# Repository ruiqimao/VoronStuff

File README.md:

# VoronStuff
Collection of my Voron mods

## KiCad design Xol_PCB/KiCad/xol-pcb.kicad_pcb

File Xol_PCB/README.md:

# Xol PCB

This is a PCB made for Armchair Engineering's [Xol Toolhead](https://github.com/Armchair-Engineering/Xol-Toolhead), featuring:
* One hotend cooling fan JST-XH connectors
* Two part cooling  fan JST-XH connectors
* One heater Micro-Fit connector
* One thermistor Micro-Fit connector
* One Neopixel JST-XH connector
* Two auxiliary JST-XH connectors
* One extruder motor connector
* Selectable fan voltage (5V, Alt, 24V)
* Integrated mount for carriage screw

## BOM

In addition to the PCB, the following connectors are needed:

| Part | Quantity | Link |
|:-:|:-:|:-:|
| Molex Micro-Fit 3.0 430451600 | 1 | [DigiKey](https://www.digikey.com/en/products/detail/molex/0430451600/531424) |
| Molex Micro-Fit 3.0 430650200 | 2 | [DigiKey](https://www.digikey.com/en/products/detail/molex/0436500200/268989) |
| JST B2B-XH-A | 4 | [DigiKey](https://www.digikey.com/en/products/detail/jst-sales-america-inc./B2B-XH-A(LF)(SN)/1651045) |
| JST B3B-XH-A | 2 | [DigiKey](https://www.digikey.com/en/products/detail/jst-sales-america-inc./B3B-XH-A/1651046) |
| JST B4B-XH-A | 1 | [DigiKey](https://www.digikey.com/en/products/detail/jst-sales-america-inc./B4B-XH-A(LF)(SN)/1651047) |

## Pinout

From the point of view looking directly at the **wiring harness connector**:

| Pin | Usage | Pin | Usage |
|:-:|:-:|:-:|:-:|
| 1 | Neopixel | 9 | Hotend voltage |
| 2 | Part cooling fan ground | 10 | Hotend ground |
| 3 | Hotend fan ground | 11 | Alt voltage |
| 4 | Thermistor ground | 12 | Thermistor |
| 5 | Motor A1 | 13 | Motor B1 |
| 6 | Motor A2 | 14 | Motor B2 |
| 7 | Ground | 15 | Auxilary 1 |
| 8 | 5V | 16 | Auxiliary 2 |

## Selectable fan voltage

There are two sets of solder jumpers, one for each type of fan, that should be bridged to select the fan voltage.

## Extruder compatibility
The PCB and strain relief are designed with only the [Sherpa Mini](https://github.com/Annex-Engineering/Sherpa_Mini-Extruder) in mind. **Usage with other extruders may require the motor connector to be swapped to the back side.**

## Distribution board
Xol PCB is compatible with the [Xol distribution board](https://store.annex.engineering/collections/pcbs/products/carabiner-distribution-board-for-xol-toolhead) from Annex Engineering. See additional documentation [here](https://github.com/Annex-Engineering/Carabiner-Docs/tree/main/carabiner-distributor_xol).

### Alternatives
* A second Xol PCB can be used as a distribution board.
* The [Carabiner distribution board](https://github.com/Annex-Engineering/Carabiner-Docs/tree/main/carabiner-distributor) can be used as labeled with the following changes:

  | Distribution PCB | Xol PCB |
  |:-:|:-:|
  | ThChamb | RGB |
  | A1| GND |
  | A2 | AUX1 |
  | A3 | AUX2 |
  | A4 | 5V |

  Additional documentation [here](https://github.com/Annex-Engineering/Carabiner-Docs/tree/main/carabiner-distributor).

## Wiring harness

Xol PCB is compatible with the [Carabiner wiring harness](https://store.annex.engineering/products/carabiner-wiring-harness) from Annex Engineering. The long version is 1200mm, which may not sufficient for some printers.

| Printer | Compatible with Carabiner Harness |
|:-:|:-:|
| Trident 250mm | Yes |
| Trident 300mm | Yes |
| Trident 350mm | Likely (untested) |
| V2.4 250mm | Yes |
| V2.4 300mm | Yes with horizontal Z chain |
| V2.4 350mm | Unlikely (untested) |

### Alternatives

* **(Recommended)** Custom length Carabiner harness from [Annex Engineering](https://store.annex.engineering/collections/pcbs/products/carabiner-wiring-harness-custom-length-kit)
* **(Recommended)** 2.2 meter alternative from [Raven Mech](https://www.ravenmech.com/products/carabiner-pinned-cable-harness)
* Repin a 14+2 Stealthburner wiring harness (e.g. [14-pin](https://www.fabreeko.com/products/ldo-v2-4-or-trident-ptfe-toolhead-cable-1-9m-350mm-sized-build?variant=43114275537151) + [2-pin](https://kb-3d.com/store/printer-specific-harnesses/474-linneo-led-extension-harness-voron-stealth-burner-1642910819052.html) + [2x Molex Micro-Fit 3.0 0430251600](https://www.digikey.com/en/products/detail/molex/0430251600/531406?utm_adgroup=&utm_source=google&utm_medium=cpc&utm_campaign=PMax%20Supplier_Focus%20Supplier&utm_term=&utm_content=&gclid=EAIaIQobChMIsoGBzZrzgAMVJzmtBh1heQdKEAQYASABEgKG5PD_BwE))

## Beacon compatibility

The two AUX pins can be used for Beacon D- and D+ lines with some caveats:
* It is an untested use case
* There will be no more AUX pins left for endstop or filament sensors
* The traces are routed over ground plane splits
* 5V must be supplied from VBUS, meaning any fans running off of 5V will be powered by VBUS
* Only compatible with Annex harness, which has a twisted wire pair for D- and D+

## Purchasing

Xol PCB can currently be purchased from:

* :us: [X.R. Bunker](https://xrbunker.works/products/xol-toolhead-board-ruiqimao)
* :us: [Fabreeko](https://www.fabreeko.com/products/xol-toolhead-board-by-ruiqimao)
* :us: [West3D](https://west3d.com/products/xol-toolhead-pcb)
* :us: [Annex Engineering](https://store.annex.engineering/products/xol-toolhead-pcb)
* :canada: [NorthPrint3D](https://northprint3d.ca/product/xol-toolhead-toolboard-pcb)
* :uk: [JB3D](https://jb3d.uk/product/xol-toolhead-pcb-by-ruiqimao)
* :eu: [Lab4450](https://lab4450.com/product/xol-toolhead-board)

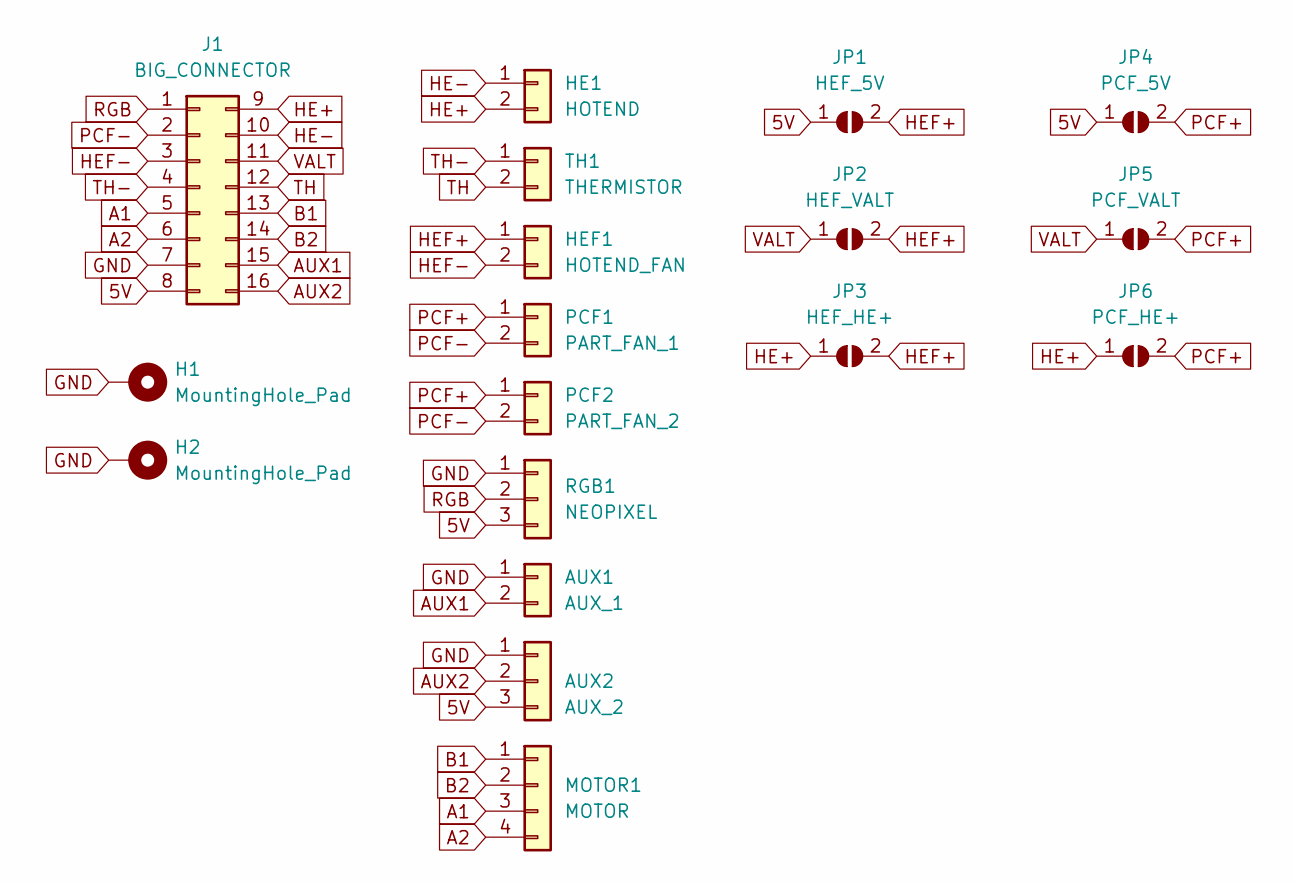
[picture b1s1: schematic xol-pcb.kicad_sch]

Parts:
AUX1: AUX_1; JST_XH_B2B-XH-A_1x02_P2.50mm_Vertical
AUX2: AUX_2; JST_XH_B3B-XH-A_1x03_P2.50mm_Vertical
H1, H2: MountingHole_Pad; MountingHole_3.2mm_M3_Pad
HE1: HOTEND; Molex_Micro-Fit_3.0_43650-0200_1x02_P3.00mm_Horizontal
HEF1: HOTEND_FAN; JST_XH_B2B-XH-A_1x02_P2.50mm_Vertical
J1: BIG_CONNECTOR; Molex_Micro-Fit_3.0_43045-1600_2x08_P3.00mm_Horizontal
JP1: HEF_5V; SolderJumper-2_P1.3mm_Open_TrianglePad1.0x1.5mm
JP2: HEF_VALT; SolderJumper-2_P1.3mm_Open_TrianglePad1.0x1.5mm
JP3: HEF_HE+; SolderJumper-2_P1.3mm_Open_TrianglePad1.0x1.5mm
JP4: PCF_5V; SolderJumper-2_P1.3mm_Open_TrianglePad1.0x1.5mm
JP5: PCF_VALT; SolderJumper-2_P1.3mm_Open_TrianglePad1.0x1.5mm
JP6: PCF_HE+; SolderJumper-2_P1.3mm_Open_TrianglePad1.0x1.5mm
MOTOR1: MOTOR; JST_XH_B4B-XH-A_1x04_P2.50mm_Vertical
PCF1: PART_FAN_1; JST_XH_B2B-XH-A_1x02_P2.50mm_Vertical
PCF2: PART_FAN_2; JST_XH_B2B-XH-A_1x02_P2.50mm_Vertical
RGB1: NEOPIXEL; JST_XH_B3B-XH-A_1x03_P2.50mm_Vertical
TH1: THERMISTOR; Molex_Micro-Fit_3.0_43650-0200_1x02_P3.00mm_Horizontal

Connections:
5V: AUX2.3, J1.8, JP1.1 (A), JP4.1 (A), RGB1.3
A1: J1.5, MOTOR1.3
A2: J1.6, MOTOR1.4
AUX1: AUX1.2, J1.15
AUX2: AUX2.2, J1.16
B1: J1.13, MOTOR1.1
B2: J1.14, MOTOR1.2
GND: AUX1.1, AUX2.1, H1.1, H2.1, J1.7, RGB1.1
HE+: HE1.2, J1.9, JP3.1 (A), JP6.1 (A)
HE-: HE1.1, J1.10
HEF+: HEF1.1, JP1.2 (B), JP2.2 (B), JP3.2 (B)
HEF-: HEF1.2, J1.3
PCF+: JP4.2 (B), JP5.2 (B), JP6.2 (B), PCF1.1, PCF2.1
PCF-: J1.2, PCF1.2, PCF2.2
RGB: J1.1, RGB1.2
TH: J1.12, TH1.2
TH-: J1.4, TH1.1
VALT: J1.11, JP2.1 (A), JP5.1 (A)

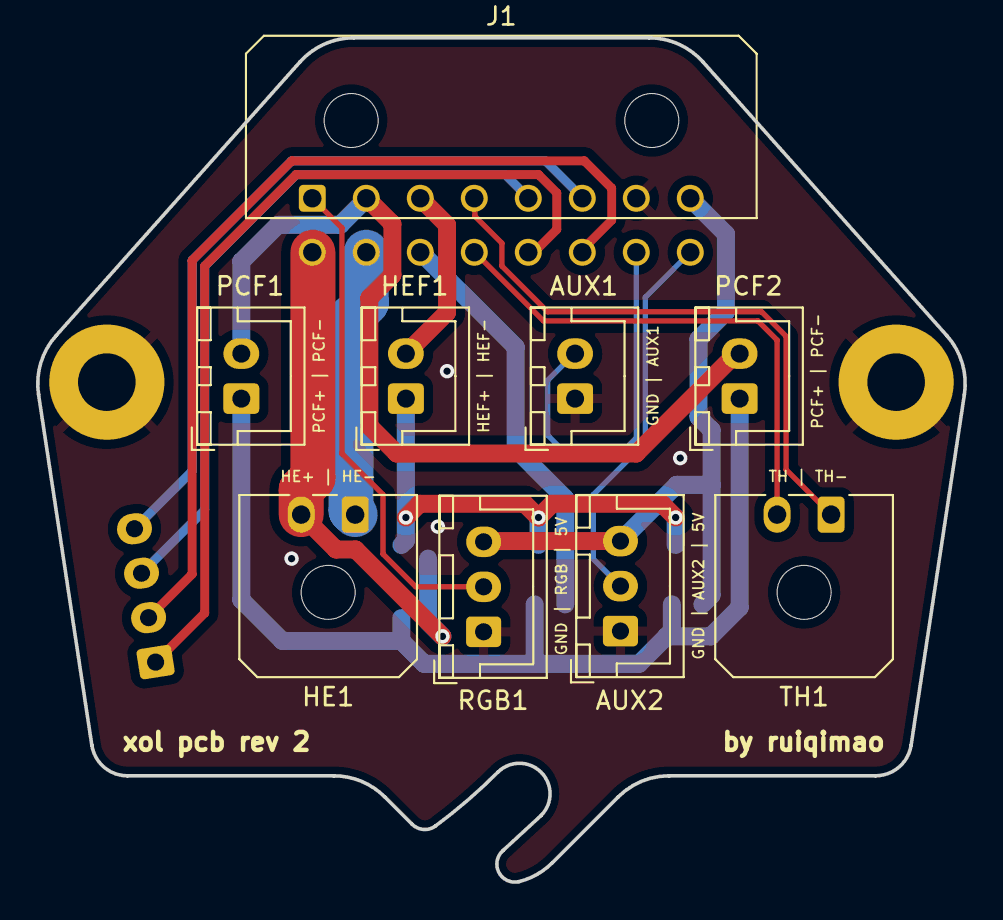
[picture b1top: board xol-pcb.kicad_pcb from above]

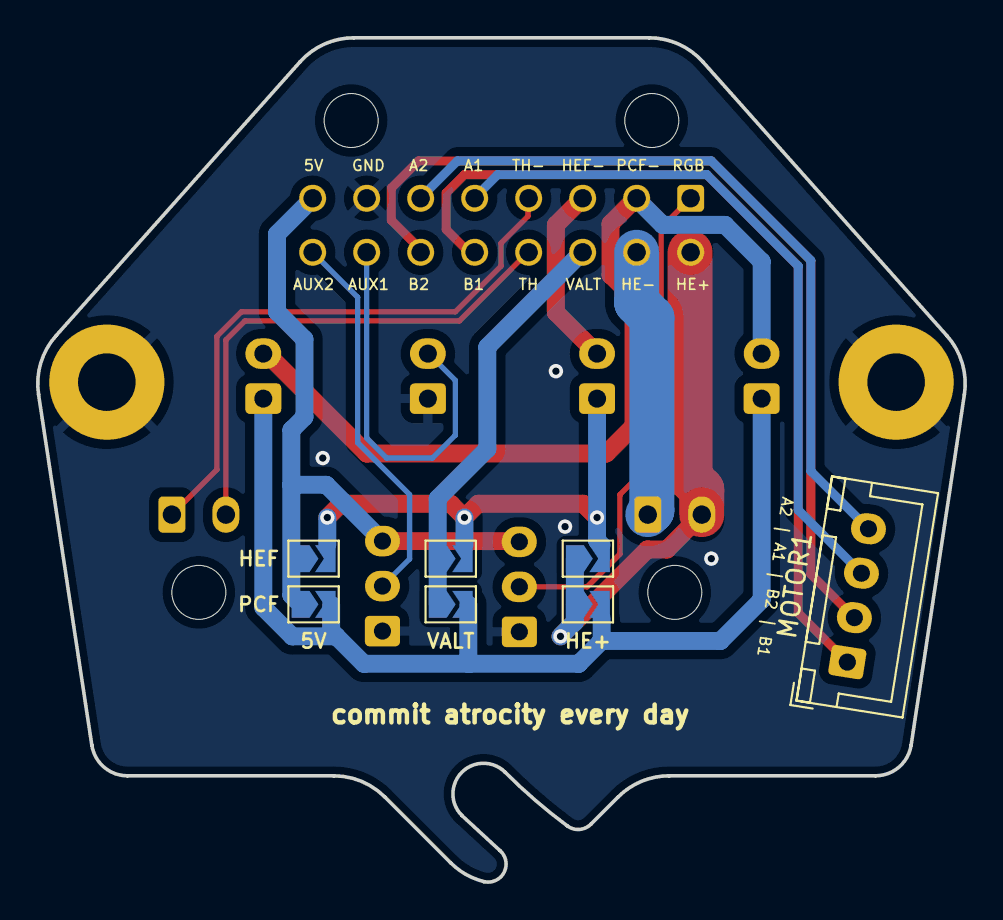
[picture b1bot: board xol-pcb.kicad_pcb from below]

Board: 2 copper layers, 51.5 x 46.9 mm, 18 parts (7 on the bottom side), 18 nets.

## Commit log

2022-08-24 Add MiniAS Lower Strain Relief
2022-08-24 Add README for MiniAS Lower Strain Relief
2022-08-24 Fix image path
2022-08-24 Reorganize files
2022-08-24 Reorient STL
2022-08-27 Add V0 display timeout
2022-08-27 Create README for V0 display timeout
2022-08-27 Add DISABLE_DISPLAY_TIMEOUT macro
2022-09-11 Add Trident Skirt Klipper Expander
2022-09-11 Fix STL orientation
2022-09-11 Create README.md for V0 Trident Skirt Klipper Expander
2022-09-20 Add files for rainbow matchstick mount
2022-09-20 Fix diffuser print count
2022-09-20 Create README.md for rainbow matchstick mount
2022-11-12 Add files for daylight stick mount
2022-11-12 Create README for daylight stick mount
2022-11-12 Fix wording
2022-12-04 Add files for T0 Waveshare skirt
2022-12-04 Create README for T0 Waveshare skirt
2022-12-04 Add instructions for foot assembly
2022-12-04 Add links to Waveshare 4.3" display
2023-04-07 Add files for Annex handles
2023-04-07 Add missing block STL
2023-04-14 Add files for B0 handles
2023-04-14 Create README.md for B0 handles
2023-07-31 Move outdated files to Archive
2023-07-31 Create README.md for Archive
2023-07-31 Add files for Xol PCB
2023-07-31 Add front and back images
2023-07-31 Create README.md for Xol PCB
2023-07-31 Fix 2-pin Micro-fit in BOM
2023-08-04 Add notes about Beacon compatibility
2023-08-23 Update Xol PCB README with wiring clarifications
2023-08-23 Add missing parenthesis
2023-09-06 Add files for Pandora's Summit
    Zip CAD to lower file size
2023-09-07 Add Pandora's Summit render
2023-09-07 Create README.md for Pandora's Summit
2023-09-19 Update Xol PCB README.md
    Clarified Carabiner distribution PCB to Xol PCB mapping
    Updated compatibility chart
2023-09-19 Update Xol PCB README.md
    Add RavenMech harness alternative
    Clarify Beacon compatibility with Annex harness
    Add purchasing links
2023-10-20 Fix typo and add West3D as vendor
2024-07-17 Add links to Carabiner docs
2025-04-05 Add NorthPrint3D to vendor list
